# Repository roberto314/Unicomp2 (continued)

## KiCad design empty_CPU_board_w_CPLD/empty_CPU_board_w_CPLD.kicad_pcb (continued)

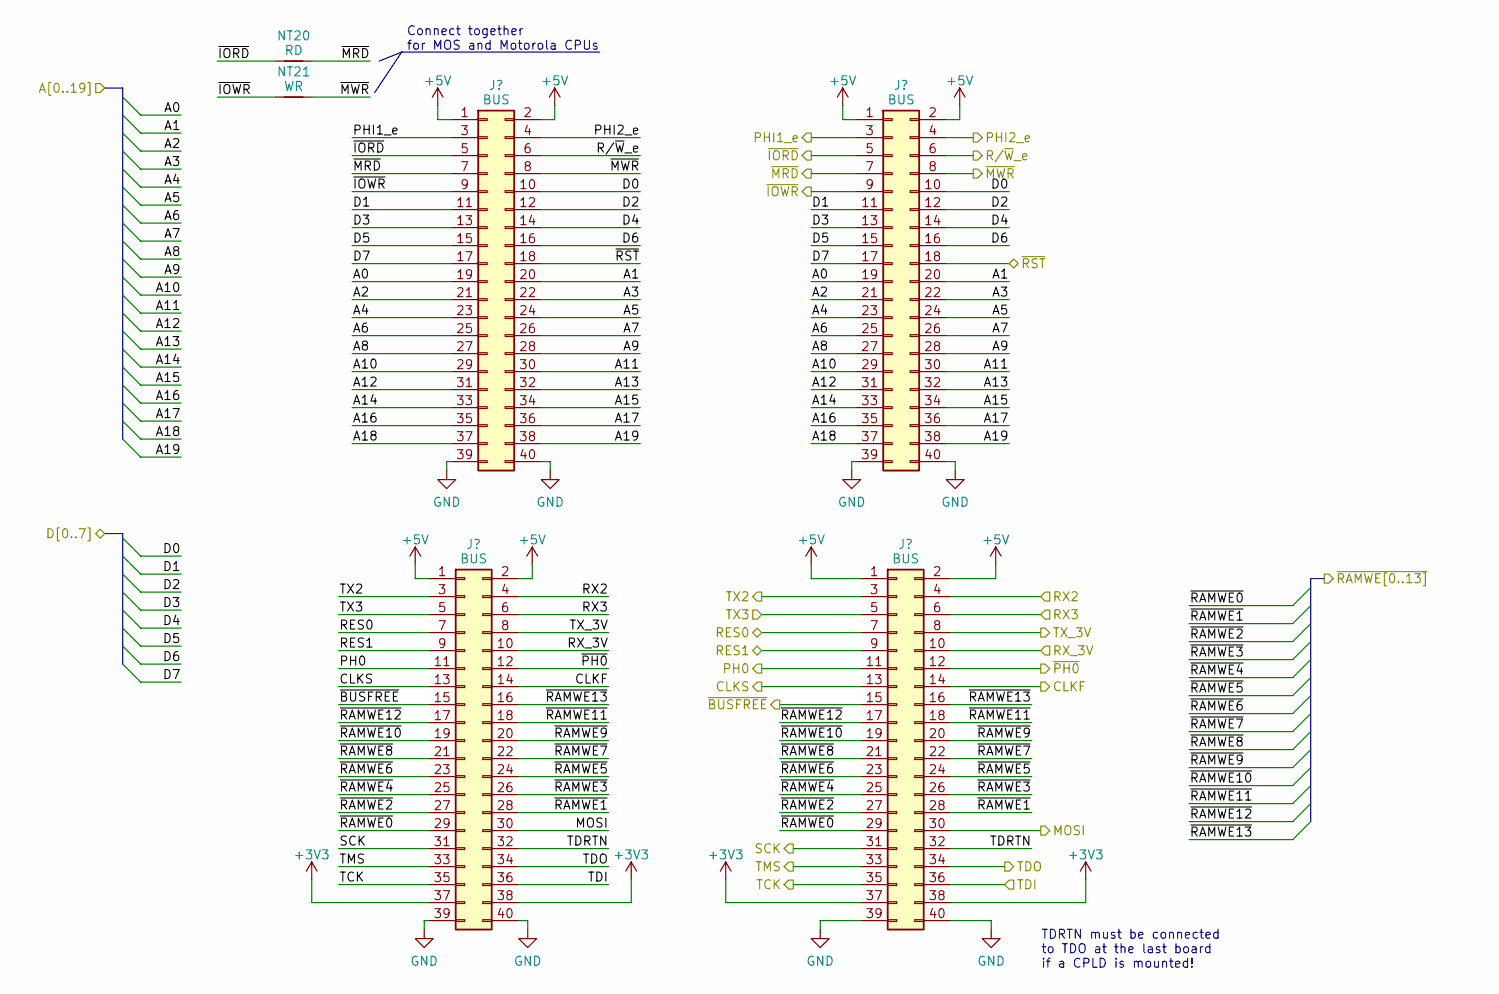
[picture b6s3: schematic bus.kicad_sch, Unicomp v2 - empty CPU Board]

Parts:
J1, J2, J3, J4: BUS; PinSocket_2x20_P2.54mm_Vertical
NT20: RD; NetTie-2_SMD_Pad0.5mm
NT21: WR; NetTie-2_SMD_Pad0.5mm

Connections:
+3V3: J2.37, J2.38, J4.37, J4.38; also elsewhere on the board
+5V: J1.1, J1.2, J2.1, J2.2, J3.1, J3.2, J4.1, J4.2; also elsewhere on the board
/A0: J1.19, J3.19; also elsewhere on the board
/A1: J1.20, J3.20; also elsewhere on the board
/A2: J1.21, J3.21; also elsewhere on the board
/A3: J1.22, J3.22; also elsewhere on the board
/A4: J1.23, J3.23; also elsewhere on the board
/A5: J1.24, J3.24; also elsewhere on the board
/A6: J1.25, J3.25; also elsewhere on the board
/A7: J1.26, J3.26; also elsewhere on the board
/A8: J1.27, J3.27; also elsewhere on the board
/A9: J1.28, J3.28; also elsewhere on the board
/A10: J1.29, J3.29; also elsewhere on the board
/A11: J1.30, J3.30; also elsewhere on the board
/A12: J1.31, J3.31; also elsewhere on the board
/A13: J1.32, J3.32; also elsewhere on the board
/A14: J1.33, J3.33; also elsewhere on the board
/A15: J1.34, J3.34; also elsewhere on the board
/A16: J1.35, J3.35
/A17: J1.36, J3.36
/A18: J1.37, J3.37
/A19: J1.38, J3.38
/Bus/TDRTN: J2.32, J4.32
/CLKF: J2.14, J4.14; also elsewhere on the board
/CLKS: J2.13, J4.13
/D0: J1.10, J3.10; also elsewhere on the board
/D1: J1.11, J3.11; also elsewhere on the board
/D2: J1.12, J3.12; also elsewhere on the board
/D3: J1.13, J3.13; also elsewhere on the board
/D4: J1.14, J3.14; also elsewhere on the board
/D5: J1.15, J3.15; also elsewhere on the board
/D6: J1.16, J3.16; also elsewhere on the board
/D7: J1.17, J3.17; also elsewhere on the board
/MOSI: J2.30, J4.30; also elsewhere on the board
/PH0: J2.11, J4.11; also elsewhere on the board
/PHI1_e: J1.3, J3.3; also elsewhere on the board
/PHI2_e: J1.4, J3.4; also elsewhere on the board
/RES0: J2.7, J4.7
/RES1: J2.9, J4.9
/RX1: J2.10, J4.10
/RX2: J2.3, J4.3
/RX3: J2.5, J4.5
/R/~W_e: J1.6, J3.6; also elsewhere on the board
/SCK: J2.31, J4.31; also elsewhere on the board
/TCK: J2.35, J4.35; also elsewhere on the board
/TDI: J2.36, J4.36; also elsewhere on the board
/TDO: J2.34, J4.34; also elsewhere on the board
/TMS: J2.33, J4.33; also elsewhere on the board
/TX1: J2.8, J4.8
/TX2: J2.4, J4.4
/TX3: J2.6, J4.6
/~BUSFREE: J2.15, J4.15
/~IORD: J1.5, J3.5, NT20.1
/~IOWR: J1.9, J3.9, NT21.1
/~MRD: J1.7, J3.7, NT20.2; also elsewhere on the board
/~MWR: J1.8, J3.8, NT21.2; also elsewhere on the board
/~PH0: J2.12, J4.12; also elsewhere on the board
/~RAMWE0: J2.29, J4.29
/~RAMWE1: J2.28, J4.28
/~RAMWE2: J2.27, J4.27
/~RAMWE3: J2.26, J4.26
/~RAMWE4: J2.25, J4.25
/~RAMWE5: J2.24, J4.24
/~RAMWE6: J2.23, J4.23
/~RAMWE7: J2.22, J4.22
/~RAMWE8: J2.21, J4.21
/~RAMWE9: J2.20, J4.20
/~RAMWE10: J2.19, J4.19
/~RAMWE11: J2.18, J4.18
/~RAMWE12: J2.17, J4.17
/~RAMWE13: J2.16, J4.16
/~RST: J1.18, J3.18; also elsewhere on the board
GND: J1.39, J1.40, J2.39, J2.40, J3.39, J3.40, J4.39, J4.40; also elsewhere on the board

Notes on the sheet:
Connect together for MOS and Motorola CPUs
TDRTN must be connected to TDO at the last board if a CPLD is mounted!

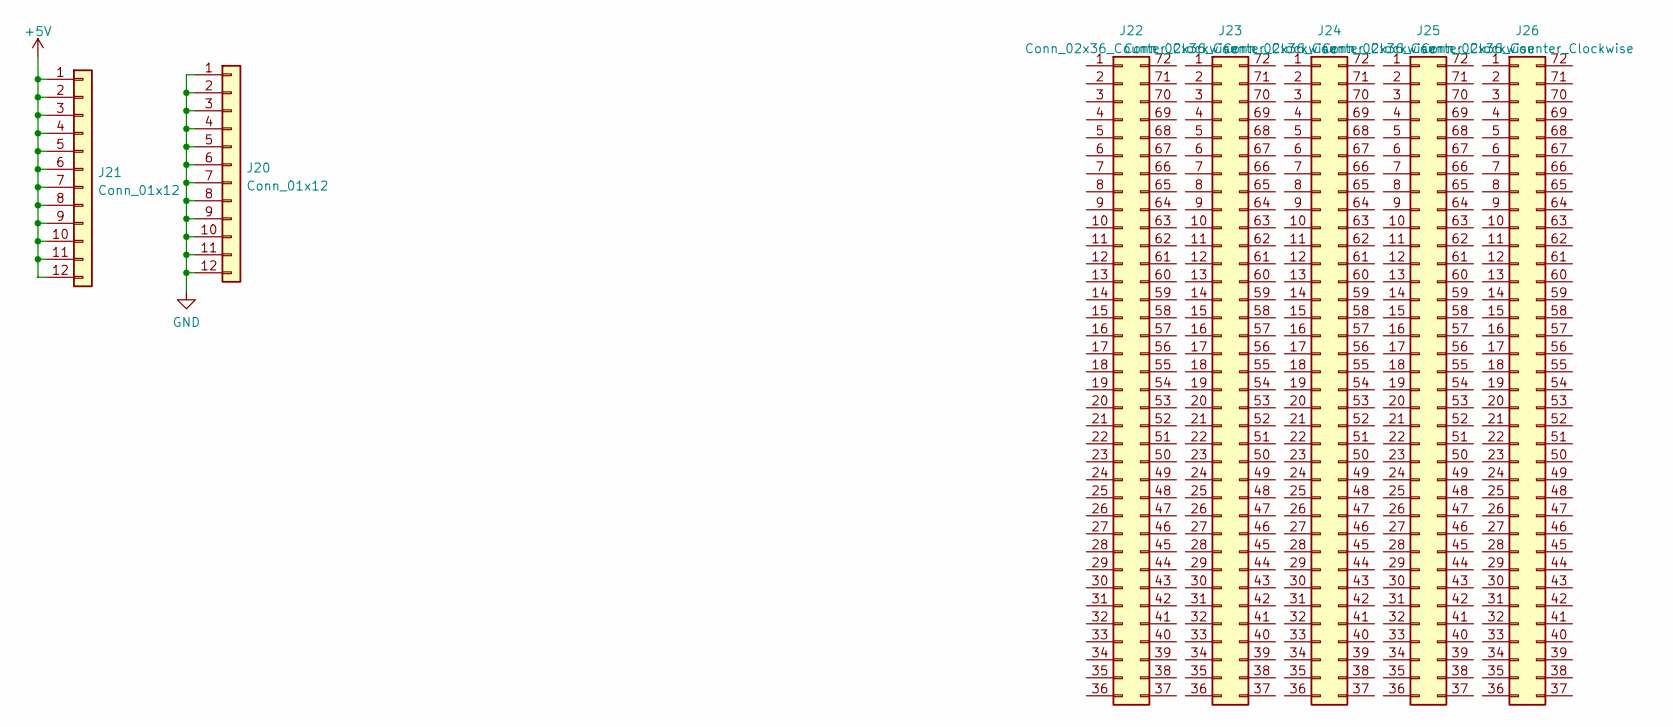
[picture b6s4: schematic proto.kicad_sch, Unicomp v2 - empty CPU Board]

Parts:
J20, J21: Conn_01x12; PinHeader_1x12_P2.54mm_Vertical
J22, J23, J24, J25, J26: Conn_02x36_Counter_Clockwise; Proto_2x36

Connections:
+5V: J21.1, J21.2, J21.3, J21.4, J21.5, J21.6, J21.7, J21.8, J21.9, J21.10, J21.11, J21.12; also elsewhere on the board
GND: J20.1, J20.2, J20.3, J20.4, J20.5, J20.6, J20.7, J20.8, J20.9, J20.10, J20.11, J20.12; also elsewhere on the board

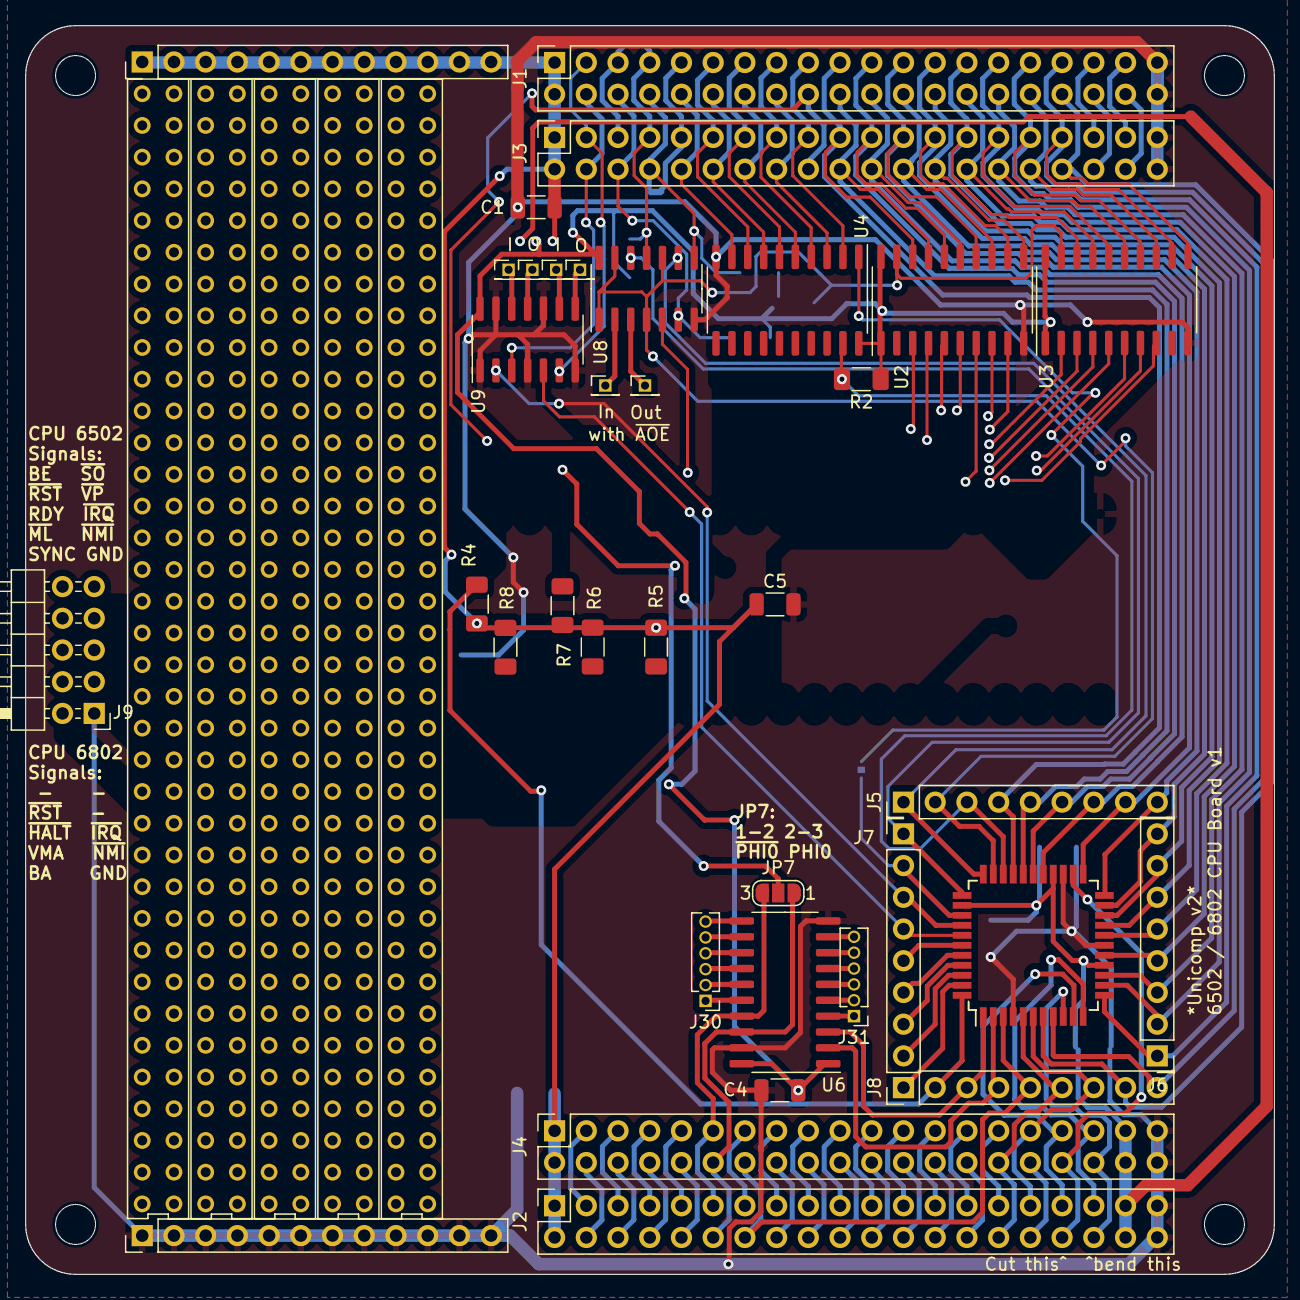
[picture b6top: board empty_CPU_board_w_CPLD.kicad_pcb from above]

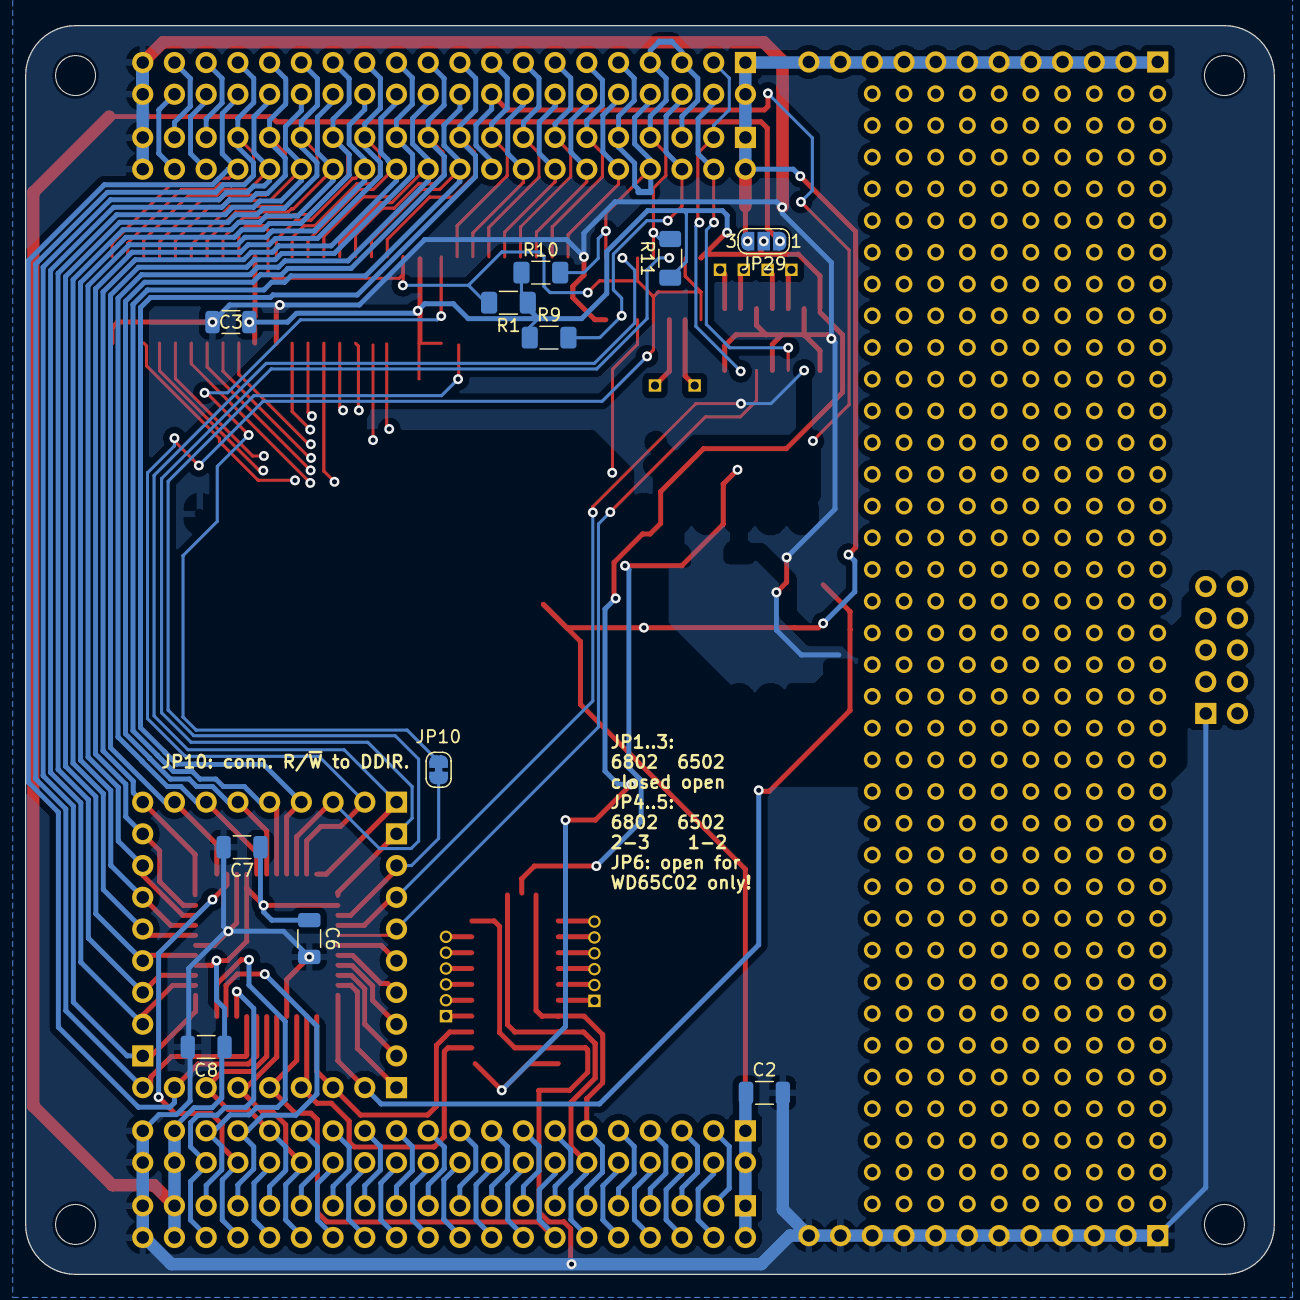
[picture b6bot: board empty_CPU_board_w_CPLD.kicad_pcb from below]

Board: 2 copper layers, 100.0 x 100.0 mm, 58 parts (13 on the bottom side), 111 nets.
